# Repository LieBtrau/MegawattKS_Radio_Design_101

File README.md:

# Overview
This FM broadcast receiver is based on the ["Radio Design 101" YouTube series](https://www.youtube.com/watch?v=r_p7AHsSOdw&list=PL9Ox3wpnB0kqekAyz6blg4YdvoEMoJNJY).

The author of the series also has a [companion website](https://ecefiles.org/rf-design/) where you can find class notes, lab assignments, etc. 

<figure>
    
    <figcaption>FM broadcast receiver block diagram from the PDF-slides of the Radio Design 101 series</figcaption>
</figure>

# Power supply
5V will be used to power the receiver so that we can keep the design relatively low power.  This unfortunately means limitations on the OIP3 of the amplifiers.  

## Project 1: Tuned RF Amplifier and Image Filter 
* [Preselector filter](./preselector_filter/Filters.ipynb)
* [RF Amplifier](./CB-CC_amplifier/CB-CC_amplifier.ipynb)
* [Altium design : LNA 1.0.2A](https://365.altium.com/files/E94FC5CA-4852-404E-B517-56AADBFE7270)

## Project 2 : Variable Frequency Oscillator
* [VFO design notes](./VFO/colpitts_clapp.ipynb)
* [Test report PBA-0000-0100](./VFO/testreport_PBA-0000-0100.ipynb)
* [KiCad design : PBA-0000-0101](https://kicanvas.org/?repo=https%3A%2F%2Fgithub.com%2FLieBtrau%2FMegawattKS_Radio_Design_101%2Ftree%2Fmain%2FVFO%2Fhardware%2Ffmosc)

## Project 3 : Mixer and IF Amplifier
* [Mixer](./IF1_mixer/mixer.ipynb)
* [Termination Insensitive Amplifier](./post_mixer_amplifier/TIA.ipynb)
* [Altium design : mixer 1.0.0](https://365.altium.com/files/F208B1A5-9C89-4744-8A48-3EA8E93C1159)

## Project 4A : Detector and Audio Amplifier : integrated design
* [FM Detector](./detector/detector.ipynb)
* [Audio Amplifier](./audio_amplifier/audio-amp.ipynb)
* [Altium design : FMDET 1.0.0A](https://365.altium.com/files/EC3D910A-1821-4A3E-BA8B-47F879EACFAB)

## Project 4B : Detector + RF frontend : discrete design
* [KiCad design : PCB-0010-0000](https://kicanvas.org/?repo=https%3A%2F%2Fgithub.com%2FLieBtrau%2FMegawattKS_Radio_Design_101%2Ftree%2Fmain%2Fdetector%2Fhardware%2Ffm-detector)

# Other resources
* [MikroE Superheterodyne FM Receivers](https://www.mikroe.com/ebooks/radio-receivers-from-crystal-set-to-stereo/superheterodyne-fm-receivers)

# Similar projects
* [Koen van Dijken : FM receiver](https://github.com/kvdijken/FM-Receiver/)
* [Phil's Valve Radio Site : Double Conversion Pulse Counting FM Superhet Receiver With 10.7 MHz First IF Stage](https://www.philsvalveradiosite.co.uk/doubleconversionpulsecountingfmtuner_1.htm)

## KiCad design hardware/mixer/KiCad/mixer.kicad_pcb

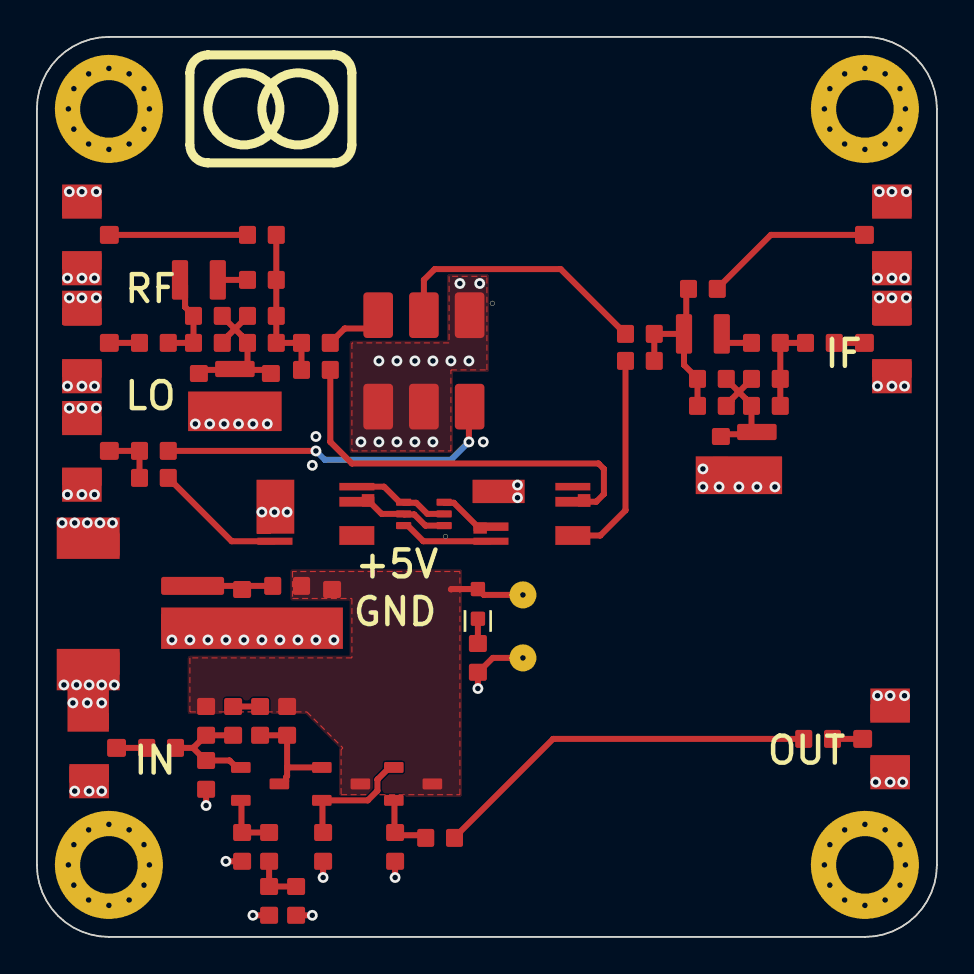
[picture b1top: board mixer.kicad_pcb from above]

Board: 4 copper layers, 50.0 x 50.0 mm, 68 parts (0 on the bottom side), 37 nets.

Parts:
C1: Capacitor 6.8pF +/-0.5pF 50V NP0 0603; 0603-C-N
C2: Capacitor 33pF +/-1% 50V NP0 0603; 0603-C-N
C3, C9, C10, C11, C12, C13, C14: Capacitor 100nF +/-10% 50V X7R 0603; 0603-C-N
C4, C5, C15, C16, C17, C18, C19, C20: Capacitor 10nF 50V NP0 0603; 0603-C-N
C6: Capacitor 3.3nF +/-10% 50V X7R 0603; 0603-C-N
C7: Capacitor 100pF +/-5% 50V NP0 0603; 0603-C-N
C8: Capacitor 47pF +/-5% 50V C0G 0603; 0603-C-N
D1: BAV99S115; SOT-363-N
D2: 150060GS84000; WL-SMCW_0603_150060xx8x000
GR1: Logo; LOGO_9x6mm
HY1: ADE-1+
J1, J2, J3, J4, J5, J7, J8: U.FL-R-SMT(10); HRS-U.FL-R-SMT_V
J6: 620102131822
L1: 744762239GA; WE-KI_1008
L2: 744758368A; WE-RFH_1008A
L3: 744762168GA; WE-KI_1008
L4: 744762118A; WE-KI_1008
MP1, MP2, MP3, MP4: MountingHole; PTH-M3D6.5_VIA-RING
Q1, Q2, Q3: MMBT3904; SOT-23-3-N
R1, R2, R3, R4, R24, R25, R26, R27: Resistor 100R +/-1% 50V 0603; 0603-R-N
R5: Resistor 10R +/-1% 50V 0603; 0603-R-N
R6, R13: Resistor 330R +/-1% 50V 0603; 0603-R-N
R7: Resistor 680R +/-1% 0.1W 0603; 0603-R-N
R8, R16: Resistor 3.6k +/-0.1W 1% 0603; 0603-R-N
R9: Resistor 1.5k +/-1% 50V 0603; 0603-R-N
R10: Resistor 47R +/-1% 0.1W 0603; 0603-R-N
R11: Resistor 91R +/-1% 0.1W 0603; 0603-R-N
R12: Resistor 18R +/-1% 0.1W 0603; 0603-R-N
R14: Resistor 470R +/-1% 50V 0603; 0603-R-N
R15: Resistor 62R +/-1% 0.1W 0603; 0603-R-N
R23: Capacitor 10nF 50V NP0 0603; 0603-C-N
TF1, TF2: ALT4532P-181-T05G; TF_STD_LAN1000_4532_6P
TP1, TP2: Testpad with multiple sizes; TP_1.5mm_0.3mmHole

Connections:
GND: C6.1, C7.1, C8.1, C9.1, C10.1, HY1.1, HY1.4, HY1.5, J1.1, J1.2, J2.1, J2.2, J3.1, J3.2, J4.1, J4.2, J5.1, J5.2, J6.2, J6.MP1, J6.MP2, J7.1, J7.2, J8.1, J8.2, L3.1, L4.1, MP1.1, MP2.1, MP3.1, MP4.1, R9.1, R11.1, R12.1, R13.1, R14.1, R15.1, R16.1, TF1.2, TF1.3, TF2.3, TP2.1
IF: C18.2, C19.2, L2.1, R3.1, R23.2, R26.1
LO: C5.1, C15.1, J1.3
NetC1_1: C1.1, L1.2
NetC2_1: C2.1, L2.2
NetC2_2: C2.2, C3.2, R4.2, R27.2
NetC3_1: C3.1, J3.3
NetC4_1: C4.1, J4.3
NetC4_2: C4.2, L1.1, R1.1, R24.1
NetC5_2: C5.2, HY1.6
NetC6_2: C6.2, L3.2, R3.2, R4.1, R26.2, R27.1
NetC7_2: C7.2, C8.2, L4.2, R1.2, R2.1, R24.2, R25.1
NetC9_2: C9.2, J6.1, R5.1
NetC11_1: C11.1, R7.1
NetC11_2: C11.2, C12.1, Q2.1, R8.1, R9.2
NetC12_2: C12.2, J7.3
NetC13_1: C13.1, R10.2
NetC13_2: C13.2, J8.3
NetC14_1: C14.1, Q2.2, R11.2
NetC14_2: C14.2, R12.2, R13.2
NetC15_2: C15.2, TF1.1
NetC16_2: C16.2, J2.3
NetC17_2: C17.2, HY1.3
NetC18_1: C18.1, HY1.2
NetC19_1: C19.1, TF2.6
NetC20_2: C20.2, TF2.5
NetD1_1: D1.1, D1.5, TF1.5
NetD1_2: D1.2, D1.4, TF1.4
NetD1_3: D1.3, TF2.2
NetD1_6: D1.6, TF2.1
NetD2_1: D2.1, R16.2
NetJ5_1: J5.3, R23.1
NetQ1_1: Q1.1, Q2.3, R6.1, R7.2
NetQ1_2: Q1.2, Q3.1, R14.2
NetQ3_2: Q3.2, R10.1, R15.2
RF: C1.2, C16.1, C17.1, C20.1, R2.2, R25.2
VCC: C10.2, D2.2, Q1.3, Q3.3, R5.2, R6.2, R8.2, TP1.1

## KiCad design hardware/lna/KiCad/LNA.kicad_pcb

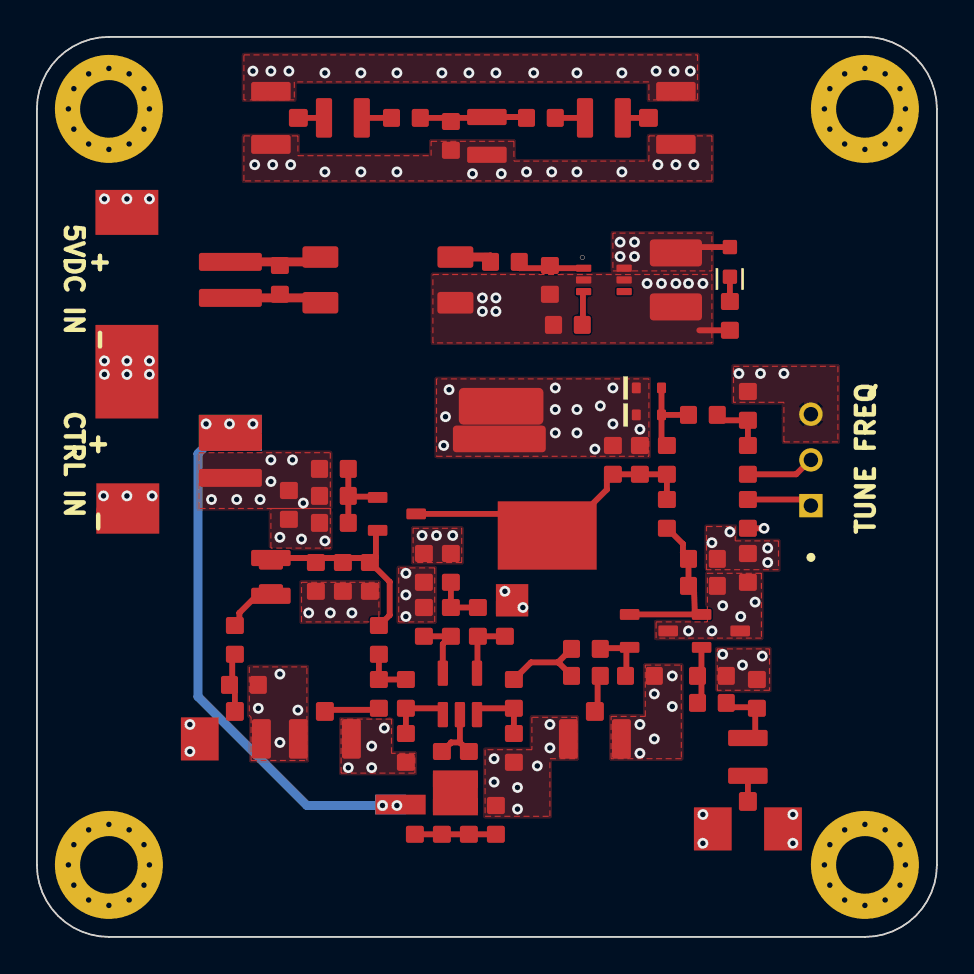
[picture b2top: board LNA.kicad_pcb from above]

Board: 4 copper layers, 50.0 x 50.0 mm, 84 parts (1 on the bottom side), 40 nets.

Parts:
C1, C2: Capacitor 6.8pF +/-0.5pF 50V NP0 0603; 0603-C-N
C3: Cap Ceramic 180pF +/-5% 100V C0G 0603; 0603-C-N
C4: Capacitor 33pF +/-5% 50V NP0 0603; 0603-C-N
C5, C6, C7, C10, C11, C12, C13, C14, C15, C17, C18, C19, C20, C21: Capacitor 10nF 50V NP0 0603; 0603-C-N
C8, C16: Capacitor 10pF +/-5% 50V NP0 0603; 0603-C-N
C9, C22: Capacitor 100nF +/-10% 50V X7R 0603; 0603-C-N
C23: Capacitor 10µF +/-10% 50V X7R 1210; WCAP-CSGP_1210_L3.2W2.5H2.5
D1, D3: SMV1220-079LF; FP-SOD523-MFG
D2: SMP1307-027LF; SOT25-N
D4: 150060GS84000; WL-SMCW_0603_150060xx8x000
FB1, FB2, FB3: 742792662; 0603-FB-N
J1, J2, J3, J4, J6, J7: U.FL-R-SMT(10); HRS-U.FL-R-SMT_V
J5, J8: 620102131822
L1, L2: 744762239GA; WE-KI_1008
L3: 744762115GA; WE-KI_1008
L4: 744912147; WE-CAIR_4248
L5: 744762227GA; WE-KI_1008
L6: 744762210GA; WE-KI_1008
L7: 744918222; WE-CAIR_5910
L8: 744222; WE-SL2_L9.2W6H5
M1: Logo; LOGO_9x6mm
MP1, MP2, MP3, MP4: MountingHole; PTH-M3D6.5_VIA-RING
Q1, Q2, Q3: MMBT5179; SOT-23-3-N
R1: Resistor 3.6k +/-0.1W 1% 0603; 0603-R-N
R2: Resistor 51k +/- 1% 50V 0603; 0603-R-N
R3: Resistor 1.5k +/-1% 50V 0603; 0603-R-N
R4, R12, R21, R25, R27: Jumper 0R <50 mOhm 1A 0603; 0603-R-N
R5: Resistor 100k +/-1% 50V 0603; 0603-R-N
R6: Resistor 6.8k +/-1% 0.1W 0603; 0603-R-N
R7: Resistor 2.7k +/-1% 0.1W 0603; 0603-R-N
R8: Resistor 510R +/-1% 0.1W 0603; 0603-R-N
R9: Resistor 22k +/-1% 50V 0603; 0603-R-N
R10: Resistor 1.2k +/-1% 50V 0603; 0603-R-N
R11, R28: Resistor 5.6k +/-1% 0.1W 0603; 0603-R-N
R13, R18, R19, R22, R24, R26: Resistor 1k +/-1% 50V 0603; 0603-R-N
R14: Resistor 270R +/-1% 50V 0603; 0603-R-N
R15, R16, R20: Resistor 560R +/-1% 0.1W 0603; 0603-R-N
R17: Jumper 0R <50 mOhm 2A 0805; 0805-R-N
R23: 3296W-1-103LF; BOUR-3296W
RV1: 8231606A; 0603-VAR-N
U1: LM66100DCKT; SOT-363-N

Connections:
+5V: C4.2, C19.1, C20.1, C21.1, C23.2, D1.1, D3.1, D4.2, L4.2, L7.2, Q1.3, Q2.3, R1.2, R2.2, R3.2, R20.1, R21.2, U1.6
FREQ_TUNE: FB2.2, R23.2
GND: C3.1, C8.2, C10.2, C12.2, C13.1, C16.1, C17.2, C18.1, C19.2, C20.2, C21.2, C22.1, C23.1, J1.1, J1.2, J2.1, J2.2, J3.1, J3.2, J4.1, J4.2, J5.MP1, J5.MP2, J6.1, J6.2, J7.1, J7.2, J8.2, J8.MP1, J8.MP2, L3.1, L8.3, MP1.1, MP2.1, MP3.1, MP4.1, R4.2, R6.1, R7.1, R8.1, R9.1, R10.1, R11.1, R15.1, R16.1, R23.3, R28.1, RV1.1, U1.2, U1.5
NetC1_1: C1.1, C2.2, C3.2, L3.2
NetC1_2: C1.2, L1.2
NetC2_1: C2.1, L2.1
NetC4_1: C4.1, C5.1, C6.2, L4.1, L7.1, Q3.3, R3.1
NetC5_2: C5.2, Q1.1, Q2.1, R1.1, R6.2
NetC6_1: C6.1, D1.2, D3.2, R5.1
NetC7_1: C7.1, Q1.2, R8.2
NetC7_2: C7.2, C8.1, L5.1
NetC9_1: C9.1, J5.2, L8.2
NetC9_2: C9.2, J5.1, L8.1
NetC10_1: C10.1, FB2.1, R5.2
NetC11_1: C11.1, R14.1, R25.2
NetC11_2: C11.2, D2.3, R16.2
NetC12_1: C12.1, Q3.1, R2.1, R9.2
NetC13_2: C13.2, FB1.2, R22.2, R26.2
NetC14_1: C14.1, J4.3, RV1.2
NetC14_2: C14.2, L6.1, R17.1
NetC15_1: C15.1, D2.1, R15.2
NetC15_2: C15.2, R12.2, R27.1
NetC16_2: C16.2, L6.2, Q3.2, R10.2, R11.2, R17.2, R27.2
NetC17_1: C17.1, D2.5, R18.1
NetC18_2: C18.2, D2.4, R19.1
NetC22_2: C22.2, FB3.1, U1.1
NetD2_2: D2.2, R13.1, R24.1
NetD4_1: D4.1, R28.2
NetFB3_2: FB3.2, L8.4
NetJ1_1: J1.3, L1.1
NetJ2_1: J2.3, L2.2
NetJ3_1: J3.3, L5.2
NetJ6_1: J6.3, R12.1
NetJ7_1: J7.3, R25.1
NetQ2_2: Q2.2, R7.2, R14.2
NetR4_1: R4.1, U1.3
NetR13_2: R13.2, R22.1, R24.2, R26.1
NetR18_2: R18.2, R19.2, R20.2
NetR21_1: R21.1, R23.1
Q_TUNE: FB1.1, J8.1

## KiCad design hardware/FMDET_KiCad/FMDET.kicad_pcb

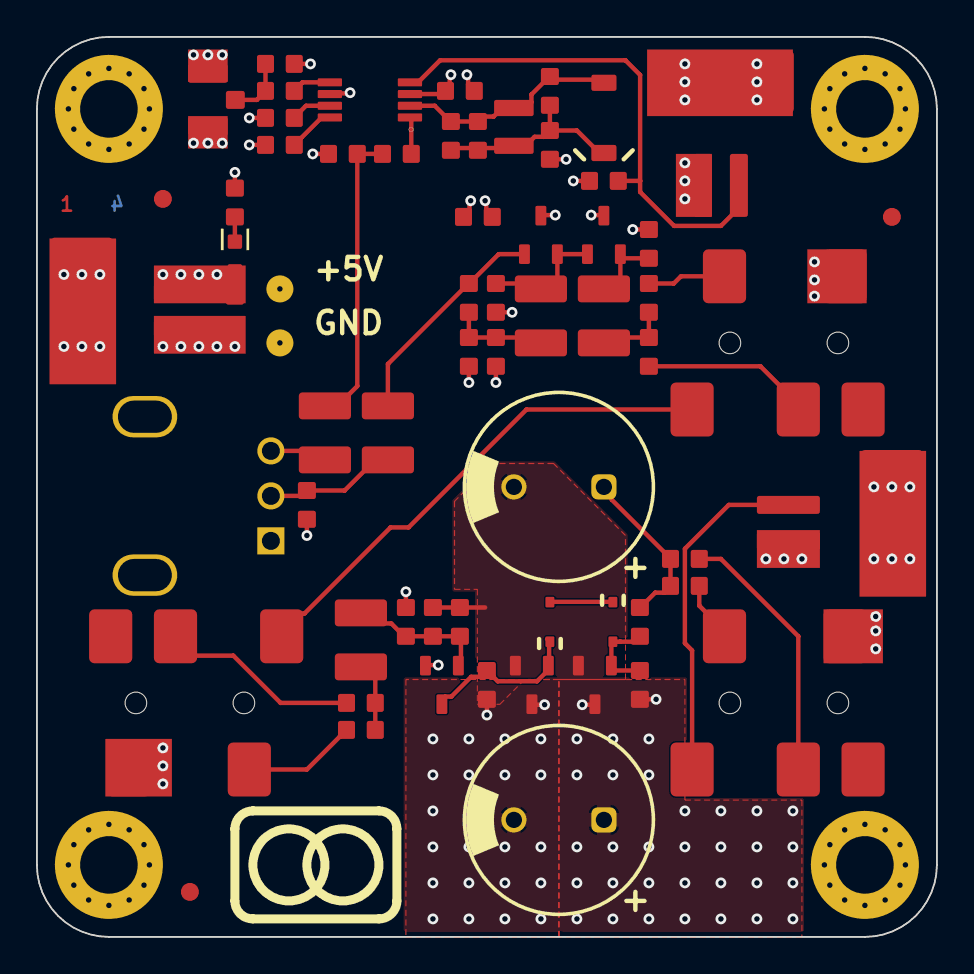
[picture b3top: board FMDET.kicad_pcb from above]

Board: 4 copper layers, 50.0 x 50.0 mm, 70 parts (0 on the bottom side), 34 nets.

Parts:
C1, C3, C4, C9, C11: Capacitor 10nF +/-10% 50V X7R 0603; 0603-C-N
C2, C8, C13: Capacitor 100nF +/-10% 50V X7R 0603; 0603-C-N
C5: SGC3S100; SGC3S100-Footprint-1
C6: Capacitor 82pF +/-5% 50V C0G 0603; 0603-C-N
C7: Capacitor 10pF +/-5% 50V NP0 0603; 0603-C-N
C10: Capacitor 1nF +/-10% 50V X7R 0603; 0603-C-N
C12, C14, C15, C16, C22: Capacitor 10µF +/-10% 50V X7R 1210; WCAP-CSGP_1210_L3.2W2.5H2.5
C17, C21: Capacitor 4.7nF +/-5% 50V X7R 0603; 0603-C-N
C18, C23: 860080275016; WCAP-ATLI_D10H16
C19: Capacitor 68pF +/-5% 50V C0G 0603; 0603-C-N
D1: 150060GS84000; WL-SMCW_0603_150060xx8x000
D2, D3: 1N4148WS; SOD323-MFG
FD1, FD2, FD3: FID1X2R
J1, J5, J7: SJ2-35863B1-SMT-TR; SJ2-35863B1-SMT-TR-Footprint-1
J2: U.FL-R-SMT(10); HRS-U.FL-R-SMT_V
J3, J4, J6: 620102131822
L1: 744762322A; WE-RFI_1008
M1: Logo; LOGO_9x6mm
MP1, MP2, MP3, MP4: MountingHole; PTH-M3D6.5_VIA-RING
PCB1: Layer_indicator_4; LayerId_4L_4x1.5mm
Q1, Q2: MMBT3904; SOT-23-3-N
Q3, Q5: ZXTN4240F-7; SOT-23-3-N
Q4: ZXTP5240F-7; SOT-23-3-N
R1: Resistor 8.2k +/-1% 0.1W 0603; 0603-R-N
R2, R3, R18, R19: Jumper 0R <50 mOhm 1A 0603; 0603-R-N
R4: Resistor 10k +/-1% 50V 0603; 0603-R-N
R5: Resistor 2.7k +/-1% 0.1W 0603; 0603-R-N
R6: Resistor 51R +/-1% 0.1W 0603; 0603-R-N
R7: Resistor 120K +/-1% 0603 0.1W; 0603-R-N
R8: PTV09A-4020F-B104; PTV09A-4020F-B104-Footprint-1
R9: Resistor 47k +/-1% 50V 0603; 0603-R-N
R10: Resistor 22k +/-1% 50V 0603; 0603-R-N
R11: Resistor 390k +/-1% 50V 0603; 0603-R-N
R12: Resistor 33k +/-1% 50V 0603; 0603-R-N
R13: Resistor 680R +/-1% 0.1W 0603; 0603-R-N
R14: Resistor 1k +/-1% 50V 0603; 0603-R-N
R15: Resistor 18k +/-1% 50V 0603; 0603-R-N
R16, R20: Resistor 2.4k +/-1% 50V 0603; 0603-R-N
R17: Resistor 5.6k +/-1% 0.1W 0603; 0603-R-N
TP1, TP2: Testpad with multiple sizes; TP_1.5mm_0.3mmHole
U1: NJM14570RB1-TE1; MSOP8

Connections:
+5V: C2.2, C8.2, C13.2, C17.2, C23.1, D1.2, J1.1, J4.1, J6.1, Q1.3, Q2.3, Q3.3, R7.2, TP1.1, U1.3
AUDIO: J5.4, J7.4
GND: C2.1, C3.1, C4.1, C8.1, C9.1, C10.1, C11.1, C13.1, C21.2, C23.2, J2.1, J2.2, J3.2, J3.MP1, J3.MP2, J4.2, J4.MP1, J4.MP2, J5.1, J6.MP1, J6.MP2, J7.1, MP1.1, MP2.1, MP3.1, MP4.1, Q4.3, Q5.2, R4.1, R6.1, R8.1, R8.S1, R8.S2, R10.1, R11.1, R12.1, R13.1, R17.1, TP2.1, U1.6
NetC1_1: C1.1, U1.5
NetC1_2: C1.2, J2.3, R6.2
NetC3_2: C3.2, U1.7
NetC4_2: C4.2, U1.8
NetC5_1: C5.1, C6.1, C7.1, C9.2, L1.1, R5.1
NetC5_2: C5.2, C6.2, C7.2, L1.2, R5.2, U1.2
NetC10_2: C10.2, J3.1, U1.4
NetC11_2: C11.2, C12.1, R1.1
NetC12_2: C12.2, R8.3
NetC14_1: C14.1, R8.2, R10.2
NetC14_2: C14.2, Q1.1, R9.1
NetC15_1: C15.1, R7.1, R9.2, R11.2
NetC15_2: C15.2, Q1.2, Q2.1, R12.2
NetC16_1: C16.1, Q2.2, R13.2
NetC16_2: C16.2, R18.2, R19.2
NetC17_1: C17.1, D2.2, Q3.1, R14.2
NetC18_1: C18.1, R2.1, R3.1, R14.1
NetC18_2: C18.2, C19.2, Q3.2, Q4.2, R15.2
NetC19_1: C19.1, C22.1, Q5.1, R15.1, R17.2
NetC21_1: C21.1, D3.1, Q4.1, Q5.3
NetC22_2: C22.2, R16.2, R20.2
NetD1_1: D1.1, R4.2
NetD2_1: D2.1, D3.2
NetJ1_2: J1.2, R3.2
NetJ1_3: J1.3, R2.2
NetJ1_4: J1.4, J6.2
NetJ5_2: J5.2, R18.1
NetJ5_3: J5.3, R19.1
NetJ7_2: J7.2, R16.1
NetJ7_3: J7.3, R20.1
NetR1_2: R1.2, U1.1

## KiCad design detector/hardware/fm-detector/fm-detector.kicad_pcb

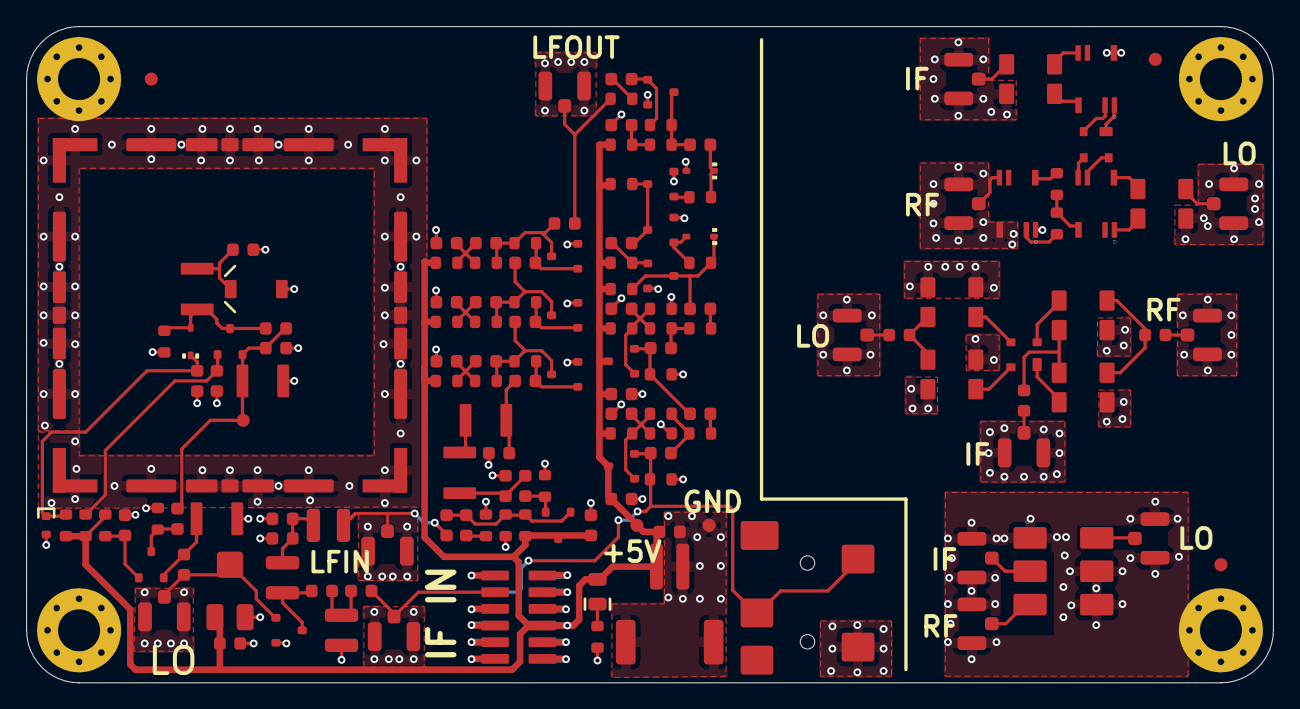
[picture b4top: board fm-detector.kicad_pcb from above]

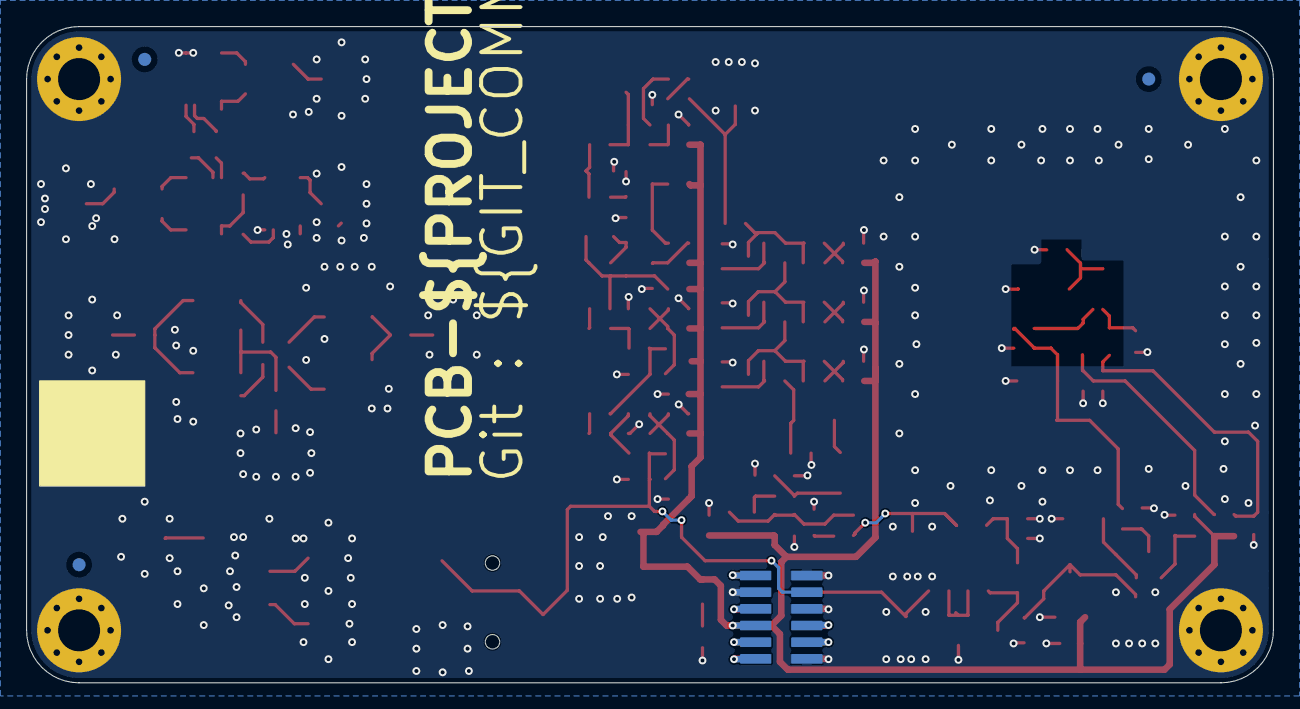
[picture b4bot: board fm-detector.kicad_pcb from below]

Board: 2 copper layers, 95.0 x 50.0 mm, 160 parts (4 on the bottom side), 84 nets.

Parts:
C1, C2, C3, C5, C7, C9, C10, C15, C16, C17, C20, C21, C23, C24, C25, C26, C27, C30, C31, C34, C41, C43, C44, C45: 100n; C_0603_1608Metric
C4, C11: 4.7n; C_0603_1608Metric
C6: 12n; C_0603_1608Metric
C8, C18, C19, C22: 150p; C_0603_1608Metric
C12, C13, C14, C28, C32: 1.5n; C_0603_1608Metric
C29, C33: 820p; C_0603_1608Metric
C35, C36, C46: 10n; C_0603_1608Metric
C37: 2p - 6p; C_Trimmer_Voltronics_JZ
C38, C39: 180p; C_0603_1608Metric
C40: 47p; C_0603_1608Metric
C42: 2p; C_0603_1608Metric
D1: GRN; LED_0805_2012Metric
D2, D6, D8: 1N4148; D_SOD-323
D3, D4: BAT15-099R; SOT-143
D7: 3V0; D_SOD-523
FD1, FD2, FD3, FD4, FD5, FD6: Fiducial; Fiducial_1mm_Mask2mm
FL1, FL2, FL3, FL4, FL5, FL6: 22µ; L_Wurth_WE-CNSW-1812
H1, H2, H3, H4: M3; MountingHole_3.2mm_M3_Pad_Via
H5, H7, H9, H10: S0991-46R; H_Harwin_S0991-46R
J1: JST PH; JST_PH_S2B-PH-SM4-TB_1x02-1MP_P2.00mm_Horizontal
J2, J3, J5, J7, J8, J9, J10, J13, J14, J15, J16, J17, J18: U.FL; U.FL_Hirose_U.FL-R-SMT-1_Vertical
J4: 3.5mm audio socket; Jack_3.5mm_SameSky_SJ2-35863B1-SMT-TR_Horizontal
J6: 2118708-2; H_TE_2118708
J11: 2x06M; PinHeader_2x06_P1.27mm_Vertical_SMD
J12: 2x06F; PinSocket_2x06_P1.27mm_Vertical_SMD
L1: 6µ8; L_Murata_LQW32FT_3225
L2, L3: 18µ; L_Murata_LQW32FT_3225
L4: 3µ9; L_Coilcraft_1008HQ_2520Metric
L5: 8µ2; L_Coilcraft_1008HQ_2520Metric
L6: 2µ7; L_Coilcraft_1008HQ_2520Metric
L8, L9: 47µ; L_Murata_LQW32FT_3225
Q1, Q2, Q4, Q5, Q6, Q7, Q8, Q9, Q10, Q11: MMBT3904; SOT-23-3
Q3: BSS138; SOT-23-3
Q12, Q13: J309; SOT-23-3
R1: 51E; R_0603_1608Metric
R2: 3K6; R_0603_1608Metric
R3: 1K5; R_0603_1608Metric
R4: 1K2; R_0603_1608Metric
R5, R8, R14, R22: 1M; R_0603_1608Metric
R6, R9, R16, R23: 100E; R_0603_1608Metric
R7, R12, R24: 3K9; R_0603_1608Metric
R10, R32: 150K; R_0603_1608Metric
R11, R21, R28, R33: 10K; R_0603_1608Metric
R13, R38, R41: 100K; R_0603_1608Metric
R15: 2K7; R_0603_1608Metric
R17, R20, R40: 1K; R_0603_1608Metric
R18: 470E; R_0603_1608Metric
R19: 20K; R_0603_1608Metric
R25, R31: 39K; R_0603_1608Metric
R26, R30: 3K3; R_0603_1608Metric
R27, R29: 15K; R_0603_1608Metric
R34, R35: 0E; R_0603_1608Metric
R39, R42: 47E; R_0603_1608Metric
RV1: 10K; Potentiometer_Bourns_3314J_Vertical
T1, T2, T3: 240µ; T_Wurth_WE-STST-4532_74930000
TP1, TP2, TP3: TestPoint; TestPoint_Pad_D1.0mm
U1: ADE-1+; H_Mini-Circuits_CD636_H4.11mm

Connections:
+5V: C5.2, C25.2, C26.1, C30.2, C34.2, D1.2 (A), J1.1, J11.7, J12.7, Q1.3 (C), Q9.3 (C), Q11.3 (C), R2.2, R6.2, R9.2, R16.2, R18.2, R19.2, R20.2, R23.2, R25.2, R31.2, R39.2, R40.2, R42.2, RV1.1, TP1.1 (1_1)
+12V: J11.8, J12.8
/AUDIO: C32.1, J4.R, J4.T, J11.4, Q11.2 (E), R33.2
/Board2board/AUDIO: J11.11, J12.11
/Board2board/AUDIOVOLH: J11.10, J12.10
/Board2board/AUDIOVOLL: J11.9, J12.9
/Board2board/IF1OSC: J11.5, J12.5
/Board2board/VTUNE: J11.1, J12.1
/DBM Experiments/COTS DBM/IF: J17.1 (In), U1.2 (IF)
/DBM Experiments/COTS DBM/LO: J18.1 (In), U1.6 (LO)
/DBM Experiments/COTS DBM/RF: J16.1 (In), U1.3 (RF)
/DBM Experiments/Diode Ring Mixer Transmission Line/IF: C46.2, FL4.4, FL6.1
/DBM Experiments/Diode Ring Mixer Transmission Line/LO: C35.1, J13.1 (In)
/DBM Experiments/Diode Ring Mixer Transmission Line/RF: C36.2, J15.1 (In)
/DBM Experiments/Diode Ring Mixer/IF: FL3.2, J10.1 (In)
/DBM Experiments/Diode Ring Mixer/LO: FL1.1, J7.1 (In)
/DBM Experiments/Diode Ring Mixer/RF: J9.1 (In), T3.7
/IF: C11.1, J2.1 (In), J12.4
/IF2_amp/IF2_amp_stage_I/IN: C6.2, C10.1, L3.2
/IF2_amp/IF2_amp_stage_I/OUT: C7.1, C19.1, Q8.3 (C), R8.2, R12.1
/IF2_amp/IF2_amp_stage_II/OUT: C8.1, C21.1, Q2.3 (C), R5.2, R7.1
/IF2_amp/IF2_amp_stage_III/OUT: C22.1, C24.1, Q10.3 (C), R22.2, R24.1
/LFIN: C2.1, J3.1 (In), L6.2
/LFOUT: C24.2, J5.1 (In), R13.1
/LO: C45.2, J8.1 (In), Q3.1 (G), RV1.2
/PPM: C27.1, D8.1 (K), Q7.3 (C), R20.1, R21.2
/audio filter 1/OUT: C28.1, C31.1, Q9.2 (E), R28.2
GND: C4.1, C5.1, C6.1, C9.2, C13.1, C14.1, C16.1, C20.2, C23.2, C25.1, C26.2, C29.1, C30.1, C33.1, C34.1, C37.2, C39.1, C40.2, C41.2, C43.1, C44.2, D2.2 (A), D7.2 (A), FL1.4, FL2.3, FL2.4, FL3.3, FL4.2, FL5.1, FL5.3, FL6.2, H1.1 (1_1), H2.1 (1_1), H3.1 (1_1), H4.1 (1_1), H5.1 (1_1), H7.1 (1_1), H9.1 (1_1), H10.1 (1_1), J1.2, J1.MP (MountPin), J2.2 (Ext), J3.2 (Ext), J4.S, J5.2 (Ext), J6.1 (Shield_1), J7.2 (Ext), J8.2 (Ext), J9.2 (Ext), J10.2 (Ext), J11.2, J11.3, J11.6, J11.12, J12.2, J12.3, J12.6, J12.12, J13.2 (Ext), J14.2 (Ext), J15.2 (Ext), J16.2 (Ext), J17.2 (Ext), J18.2 (Ext), L4.1, L8.1, L9.1, Q2.2 (E), Q3.2 (S), Q4.2 (E), Q5.2 (E), Q6.2 (E), Q7.2 (E), Q8.2 (E), Q10.2 (E), R1.1, R3.1, R4.1, R10.1, R11.1, R28.1, R32.1, R33.1, R38.1, R41.1, RV1.3, T2.5, T3.1, T3.3, T3.4, TP2.1 (1_1), U1.1 (G), U1.4 (GND), U1.5 (GND)
unnamed: C1.1, R1.2
unnamed: C3.2, C4.2, L2.1
unnamed: C8.2, C9.1, R6.1, R7.2
unnamed: C11.2, C12.1, L4.2
unnamed: C13.2, C14.2, L5.2, L6.1
unnamed: C15.1, R13.2
unnamed: C16.2, R15.2, R16.1
unnamed: C19.2, C20.1, R9.1, R12.2
unnamed: C22.2, C23.1, R23.1, R24.2
unnamed: C27.2, R27.1
unnamed: C28.2, R26.1, R27.2
unnamed: C31.2, R29.1
unnamed: C32.2, R29.2, R30.1
unnamed: C35.2, FL2.1, FL5.4
unnamed: C36.1, FL4.3, FL6.3
unnamed: C37.1, C40.1, L1.1
unnamed: D1.1 (K), R11.2
unnamed: C17.2, D2.1 (K), R17.1
unnamed: D3.1, T2.1
unnamed: D3.2, T2.2
unnamed: D3.3, T1.7
unnamed: D3.4, T1.6
unnamed: D4.1, FL4.1
unnamed: D4.2, FL6.4
unnamed: D4.3, FL2.2
unnamed: D4.4, FL5.2
unnamed: C38.2, D6.2 (A), L1.2, Q12.3 (G), R38.2
unnamed: C43.2, D6.1 (K), D7.1 (K), R40.1
unnamed: D8.2 (A), Q6.1 (B), R21.1
unnamed: FL1.2, T1.5
unnamed: FL1.3, T1.1
unnamed: FL3.1, T2.7
unnamed: FL3.4, T2.3, T2.4
unnamed: C46.1, J14.1 (In)
unnamed: L2.2, L3.1
unnamed: C1.2, C2.2, Q1.1 (B), R2.1, R3.2
unnamed: C3.1, Q1.2 (E), R4.2
unnamed: C7.2, Q2.1 (B), R5.1
unnamed: C12.2, L5.1, Q3.3 (D)
unnamed: C15.2, Q4.1 (B), R14.1
unnamed: C17.1, Q4.3 (C), R14.2, R15.1
unnamed: Q5.1 (B), R17.2
unnamed: C18.1, Q5.3 (C), Q6.3 (C), R18.1
unnamed: C18.2, Q7.1 (B), R19.1
unnamed: C10.2, Q8.1 (B), R8.1
unnamed: C29.2, Q9.1 (B), R10.2, R25.1, R26.2
unnamed: C21.2, Q10.1 (B), R22.1
unnamed: C33.2, Q11.1 (B), R30.2, R31.1, R32.2
unnamed: C41.1, Q12.1 (D), R39.1
unnamed: C38.1, C39.2, C42.1, L8.2, Q12.2 (S), TP3.1 (1_1)
unnamed: C44.1, Q13.1 (D), R42.1
unnamed: C42.2, Q13.3 (G), R41.2
unnamed: C45.1, L9.2, Q13.2 (S)
unnamed: R34.1, T3.2
unnamed: R34.2, R35.2, T1.3, T1.4
unnamed: R35.1, T3.5

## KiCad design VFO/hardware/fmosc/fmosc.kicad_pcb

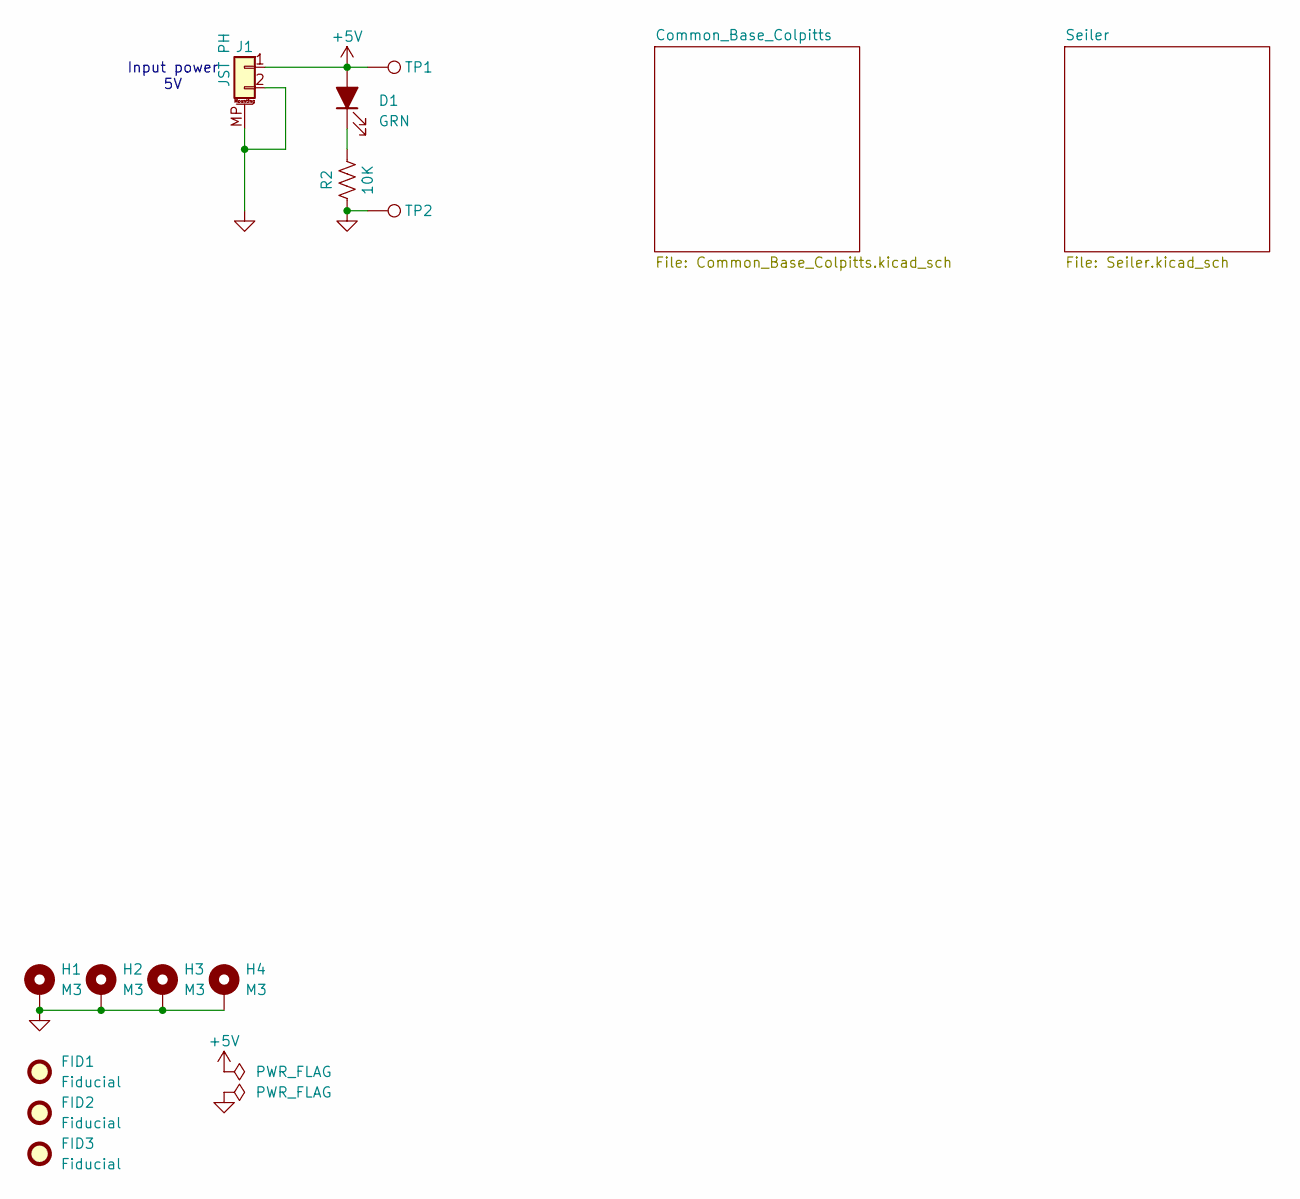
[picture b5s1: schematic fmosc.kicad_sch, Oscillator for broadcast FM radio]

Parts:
D1: GRN; LED_0805_2012Metric; MPN KT-0805G; LCSC C2297
FID1, FID2, FID3: Fiducial; Fiducial_1mm_Mask2mm
H1, H2, H3, H4: M3; MountingHole_3.2mm_M3_Pad_Via
J1: JST PH; JST_PH_S2B-PH-SM4-TB_1x02-1MP_P2.00mm_Horizontal; MPN S2B-PH-SM4-TB; LCSC C295747
R2: 10K; R_0603_1608Metric; Tolerance 1%; MPN RC0603FR-0710KL; LCSC C25804
TP1, TP2: TestPoint; TestPoint_Pad_D1.0mm

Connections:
+5V: D1.2 (A), J1.1, TP1.1; also elsewhere on the board
GND: H1.1, H2.1, H3.1, H4.1, J1.2, J1.MP (MountPin), R2.1, TP2.1; also elsewhere on the board
unnamed: D1.1 (K), R2.2

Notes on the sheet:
Input power 5V

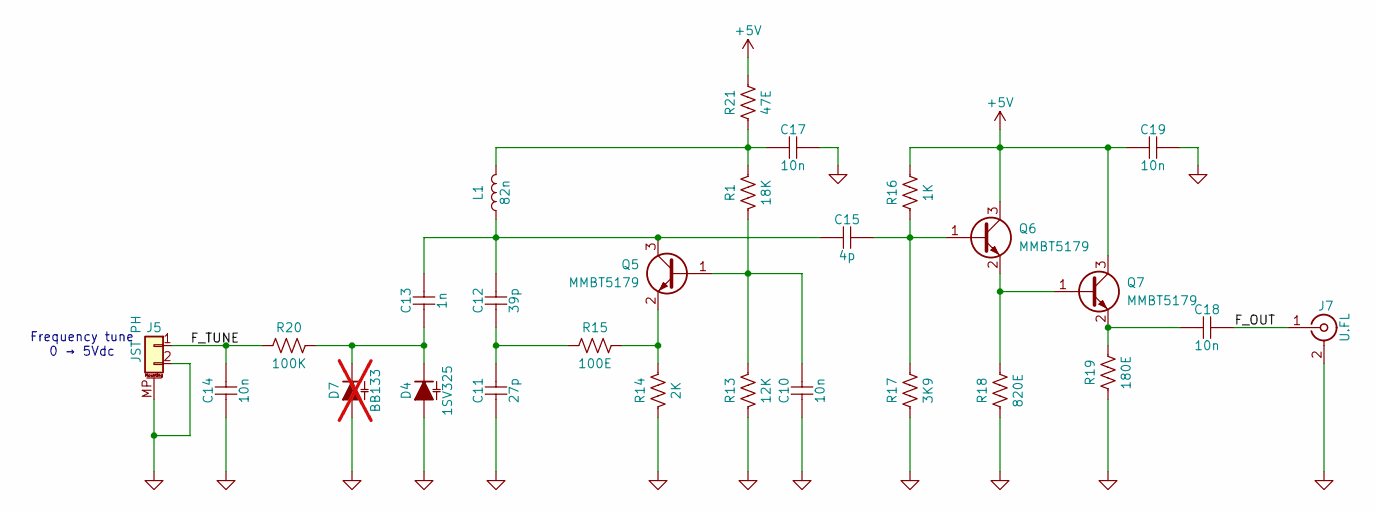
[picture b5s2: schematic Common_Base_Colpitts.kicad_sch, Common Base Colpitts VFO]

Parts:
C10, C14, C17, C18, C19: 10n; C_0603_1608Metric; Voltage 50V; Tolerance ±10%; MPN GCM188R71H103KA37D; LCSC C57112
C11: 27p; C_0603_1608Metric; Voltage 50V; Tolerance ±5%; MPN C0603C270J5GACTU; LCSC C107045
C12: 39p; C_0603_1608Metric; Voltage 50V; Tolerance ±5%; MPN C0603C390J5GACTU; LCSC C107049
C13: 1n; C_0603_1608Metric; Voltage 50V; Tolerance ±10%; MPN CL10B102KB8NNNC; LCSC C1588
C15: 4p; C_0603_1608Metric; Voltage 50V; Tolerance ±0.25pF; MPN 0603CG4R0C500NT; LCSC C1668
D4: 1SV325; D_SOD-523; Voltage 10V; MPN 1SV325,H3F(T; LCSC C4153758
D7: BB133; D_SOD-323; Voltage 30V; MPN BB133; LCSC C5334579; not fitted
J5: JST PH; JST_PH_S2B-PH-SM4-TB_1x02-1MP_P2.00mm_Horizontal; MPN S2B-PH-SM4-TB; LCSC C295747
J7: U.FL; U.FL_Hirose_U.FL-R-SMT-1_Vertical; MPN U.FL-R-SMT-1(10); LCSC C5137195
L1: 82n; L_Wurth_WE-CAIR-4248; MPN 744912182; LCSC C5178935
Q5, Q6, Q7: MMBT5179; SOT-23-3; MPN MMBT5179; LCSC C416012
R1: 18K; R_0603_1608Metric; Tolerance 1%; MPN RC0603FR-0718KL; LCSC C25810
R13: 12K; R_0603_1608Metric; Tolerance 1%; MPN RC0603FR-0712KL; LCSC C22790
R14: 2K; R_0603_1608Metric; Tolerance 1%; MPN RC0603FR-072KL; LCSC C22975
R15: 100E; R_0603_1608Metric; Tolerance 1%; MPN RC0603FR-07100RL; LCSC C22775
R16: 1K; R_0603_1608Metric; Tolerance 1%; MPN RC0603FR-071KL; LCSC C21190
R17: 3K9; R_0603_1608Metric; Tolerance 1%; MPN RC0603FR-133K9L; LCSC C23018
R18: 820E; R_0603_1608Metric; Tolerance 1%; MPN RC0603FR-13820RL; LCSC C23253
R19: 180E; R_0603_1608Metric; Tolerance 1%; MPN RC0603FR-07180RL; LCSC C22828
R20: 100K; R_0603_1608Metric; Tolerance 1%; MPN RC0603FR-07100KL; LCSC C25803
R21: 47E; R_0603_1608Metric; Tolerance 1%; MPN RC0603FR-0747RL; LCSC C23182

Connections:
+5V: C19.1, Q6.3 (C), Q7.3 (C), R16.2, R21.2; also elsewhere on the board
/Common_Base_Colpitts/F_OUT: C18.2, J7.1 (In)
/Common_Base_Colpitts/F_TUNE: C14.2, J5.1, R20.1
GND: C10.2, C11.1, C14.1, C17.2, C19.2, D4.2 (A), D7.2 (A), J5.2, J5.MP (MountPin), J7.2 (Ext), R13.2, R14.2, R17.1, R18.1, R19.1; also elsewhere on the board
unnamed: C11.2, C12.1, R15.1
unnamed: C17.1, L1.2, R1.1, R21.1
unnamed: C13.1, D4.1 (K), D7.1 (K), R20.2
unnamed: C10.1, Q5.1 (B), R1.2, R13.1
unnamed: C12.2, C13.2, C15.1, L1.1, Q5.3 (C)
unnamed: Q5.2 (E), R14.1, R15.2
unnamed: C15.2, Q6.1 (B), R16.1, R17.2
unnamed: Q6.2 (E), Q7.1 (B), R18.2
unnamed: C18.1, Q7.2 (E), R19.2

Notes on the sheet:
Frequency tune 0 → 5Vdc

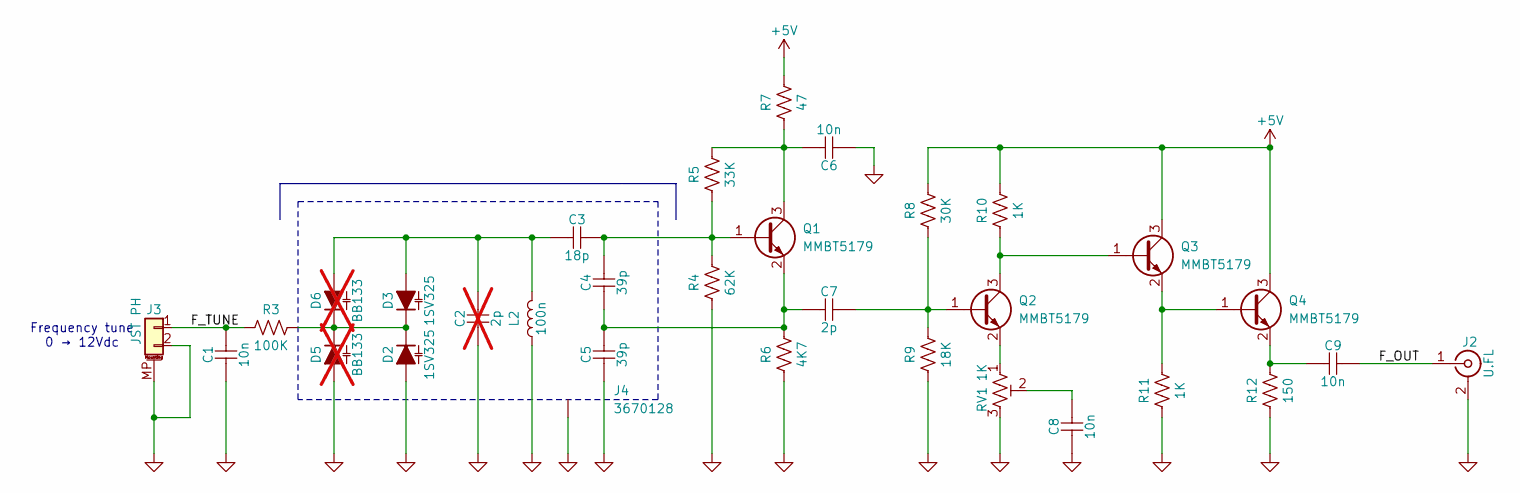
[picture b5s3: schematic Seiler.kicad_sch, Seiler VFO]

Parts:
C1, C6, C8, C9: 10n; C_0603_1608Metric; Voltage 50V; Tolerance ±10%; MPN GCM188R71H103KA37D; LCSC C57112
C2: 2p; C_0603_1608Metric; Voltage 50V; Tolerance ±0.25pF; MPN CL10C020CB8NNNC; LCSC C1650; not fitted
C3: 18p; C_0603_1608Metric; Voltage 50V; Tolerance ±5%; MPN C0603C180J5GACTU; LCSC C1647
C4, C5: 39p; C_0603_1608Metric; Voltage 50V; Tolerance ±5%; MPN C0603C390J5GACTU; LCSC C107049
C7: 2p; C_0603_1608Metric; Voltage 50V; Tolerance ±0.25pF; MPN CL10C020CB8NNNC; LCSC C1650
D2, D3: 1SV325; D_SOD-523; Voltage 10V; MPN 1SV325,H3F(T; LCSC C4153758
D5, D6: BB133; D_SOD-323; Voltage 30V; MPN BB133; LCSC C5334579; not fitted
J2: U.FL; U.FL_Hirose_U.FL-R-SMT-1_Vertical; MPN U.FL-R-SMT-1(10); LCSC C5137195
J3: JST PH; JST_PH_S2B-PH-SM4-TB_1x02-1MP_P2.00mm_Horizontal; MPN S2B-PH-SM4-TB; LCSC C295747
J4: 3670128; H_Wurth_WE-SHC-SEAMLESS-FRAME_3670128; MPN 3670128; LCSC C4365834
L2: 100n; L_Wurth_WE-CAIR-4248; MPN 744912210; LCSC C5182193
Q1, Q2, Q3, Q4: MMBT5179; SOT-23-3; MPN MMBT5179; LCSC C416012
R3: 100K; R_0603_1608Metric; Tolerance 1%; MPN RC0603FR-07100KL; LCSC C25803
R4: 62K; R_0603_1608Metric; Tolerance 1%; MPN RC0603FR-1362KL; LCSC C23221
R5: 33K; R_0603_1608Metric; Tolerance 1%; MPN RC0603FR-0733KL; LCSC C4216
R6: 4K7; R_0603_1608Metric; Tolerance 1%; MPN RC0603FR-074K7L; LCSC C23162
R7: 47; R_0603_1608Metric; Tolerance 1%; MPN RC0603FR-0747RL; LCSC C23182
R8: 30K; R_0603_1608Metric; Tolerance 1%; MPN RC0603FR-0730KL; LCSC C22984
R9: 18K; R_0603_1608Metric; Tolerance 1%; MPN RC0603FR-0718KL; LCSC C25810
R10, R11: 1K; R_0603_1608Metric; Tolerance 1%; MPN RC0603FR-071KL; LCSC C21190
R12: 150; R_0603_1608Metric; Tolerance 1%; MPN RC0603FR-07150RL; LCSC C22808
RV1: 1K; Potentiometer_Bourns_3314J_Vertical; Tolerance 20.00%; MPN 3314J-1-102E; LCSC C124640

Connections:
+5V: Q3.3 (C), Q4.3 (C), R7.2, R8.2, R10.2; also elsewhere on the board
/Seiler/F_OUT: C9.2, J2.1 (In)
/Seiler/F_TUNE: C1.2, J3.1, R3.1
GND: C1.1, C2.1, C5.1, C6.1, C8.1, D2.2 (A), D5.2 (A), J2.2 (Ext), J3.2, J3.MP (MountPin), J4.1 (Shield), L2.1, R4.1, R6.1, R9.1, R11.1, R12.1, RV1.3; also elsewhere on the board
unnamed: C8.2, RV1.2
unnamed: D2.1 (K), D3.1 (K), D5.1 (K), D6.1 (K), R3.2
unnamed: C2.2, C3.1, D3.2 (A), D6.2 (A), L2.2
unnamed: C3.2, C4.2, Q1.1 (B), R4.2, R5.1
unnamed: C6.2, Q1.3 (C), R5.2, R7.1
unnamed: C4.1, C5.2, C7.1, Q1.2 (E), R6.2
unnamed: C7.2, Q2.1 (B), R8.1, R9.2
unnamed: Q2.3 (C), Q3.1 (B), R10.1
unnamed: Q2.2 (E), RV1.1
unnamed: Q3.2 (E), Q4.1 (B), R11.2
unnamed: C9.1, Q4.2 (E), R12.2

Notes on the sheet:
Frequency tune 0 → 12Vdc

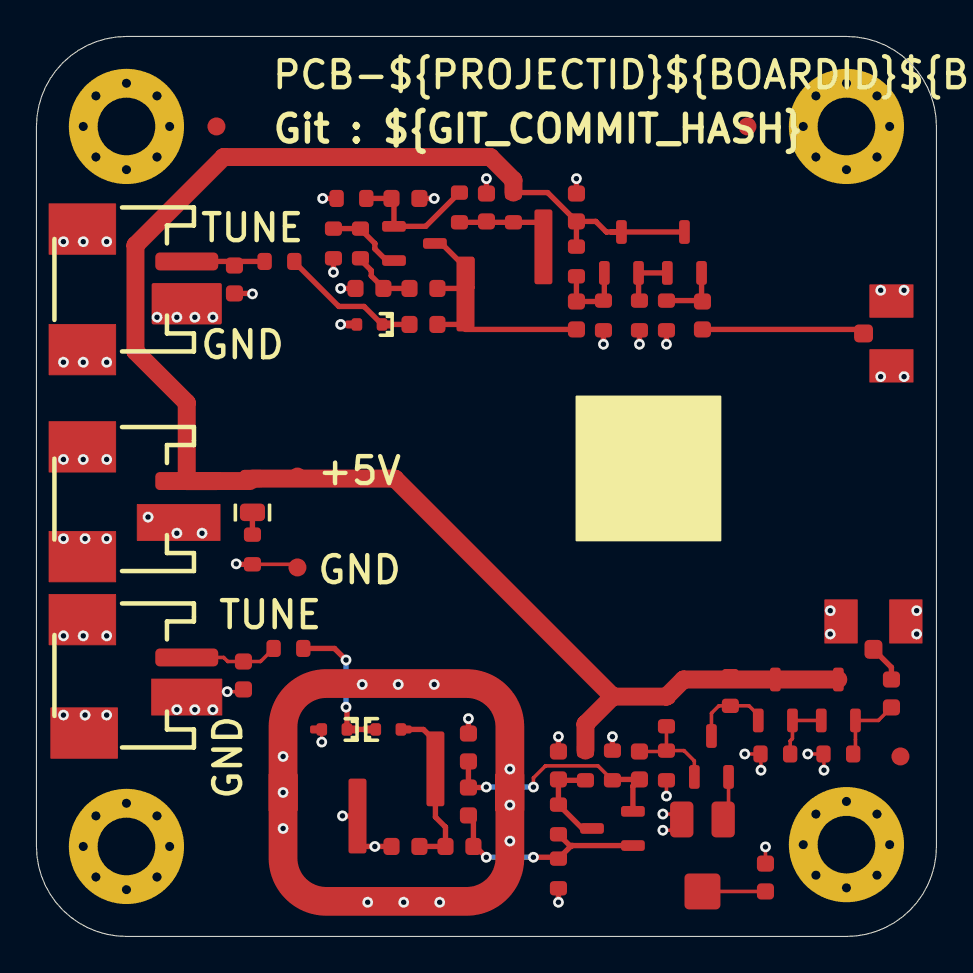
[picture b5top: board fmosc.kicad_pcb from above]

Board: 2 copper layers, 50.0 x 50.0 mm, 71 parts (0 on the bottom side), 27 nets.
